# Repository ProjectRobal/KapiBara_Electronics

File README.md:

# KapiBara Electronics Design

That repository holds all the electronics for KapiBara robot. Everything was designed using KiCAD software.

## Boards

- KANGOO - a HAT that connects to Raspberry Pi 5. It delivers +5V using on board buck converter and gives Pi ability to communicate with CAN interface, it also has built in audio codec for microphones ( not used )
- KANGOO_1 - an evolution of KANGOO design it is HAT that connects to Modus extension board, like any other module
- MODUS - an extension board that connect every modules together using standard IDC connectors
- Modus_Extension_Template - a basic template creating standard module compatible with the MODUS board
- MEGANE - a module that handles DC motors control, odometry and orientation estimation using built in IMU and external Magnetrometer
- POWER - a board using for chargin robot's accumulator, it is also responsible for power delivering to entire system
- TWINGO - a module that handles reading state of external touch sensors
- TWINGO_v1.1 - a module that handles reading state of external touch plates, touch is detected by on board RC oscillatros ( not used )

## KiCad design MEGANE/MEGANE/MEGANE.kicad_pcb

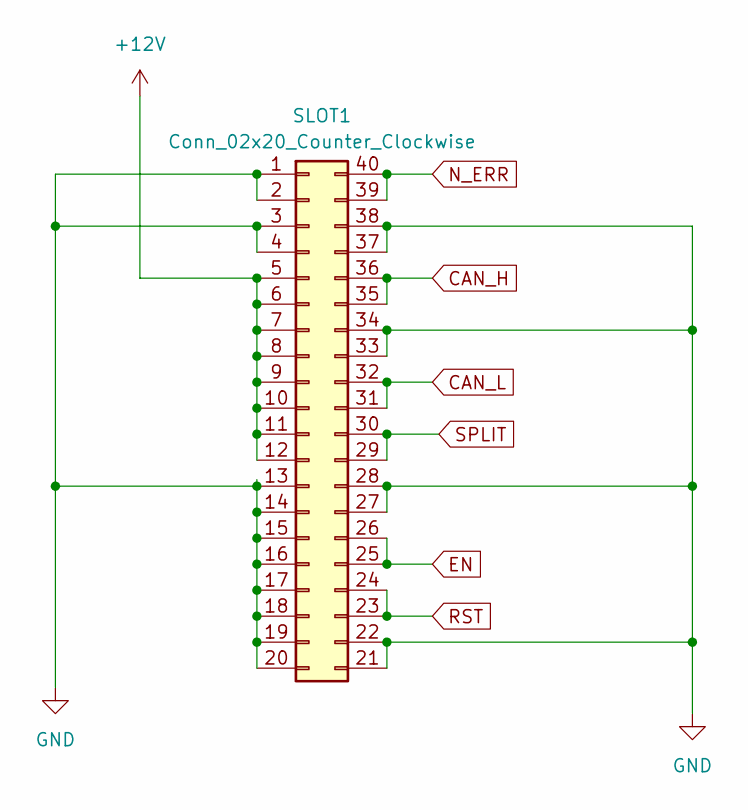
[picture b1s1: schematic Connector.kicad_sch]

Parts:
SLOT1: Conn_02x20_Counter_Clockwise; IDC-Header_2x20_P2.54mm_Horizontal

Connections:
+12V: SLOT1.5, SLOT1.6, SLOT1.7, SLOT1.8, SLOT1.9, SLOT1.10, SLOT1.11, SLOT1.12; also elsewhere on the board
CAN_H: SLOT1.35, SLOT1.36; also elsewhere on the board
CAN_L: SLOT1.31, SLOT1.32; also elsewhere on the board
EN: SLOT1.25, SLOT1.26; also elsewhere on the board
GND: SLOT1.1, SLOT1.2, SLOT1.3, SLOT1.4, SLOT1.13, SLOT1.14, SLOT1.15, SLOT1.16, SLOT1.17, SLOT1.18, SLOT1.19, SLOT1.20, SLOT1.21, SLOT1.22, SLOT1.27, SLOT1.28, SLOT1.33, SLOT1.34, SLOT1.37, SLOT1.38; also elsewhere on the board
N_ERR: SLOT1.39, SLOT1.40; also elsewhere on the board
RST: SLOT1.23, SLOT1.24; also elsewhere on the board
SPLIT: SLOT1.29, SLOT1.30; also elsewhere on the board

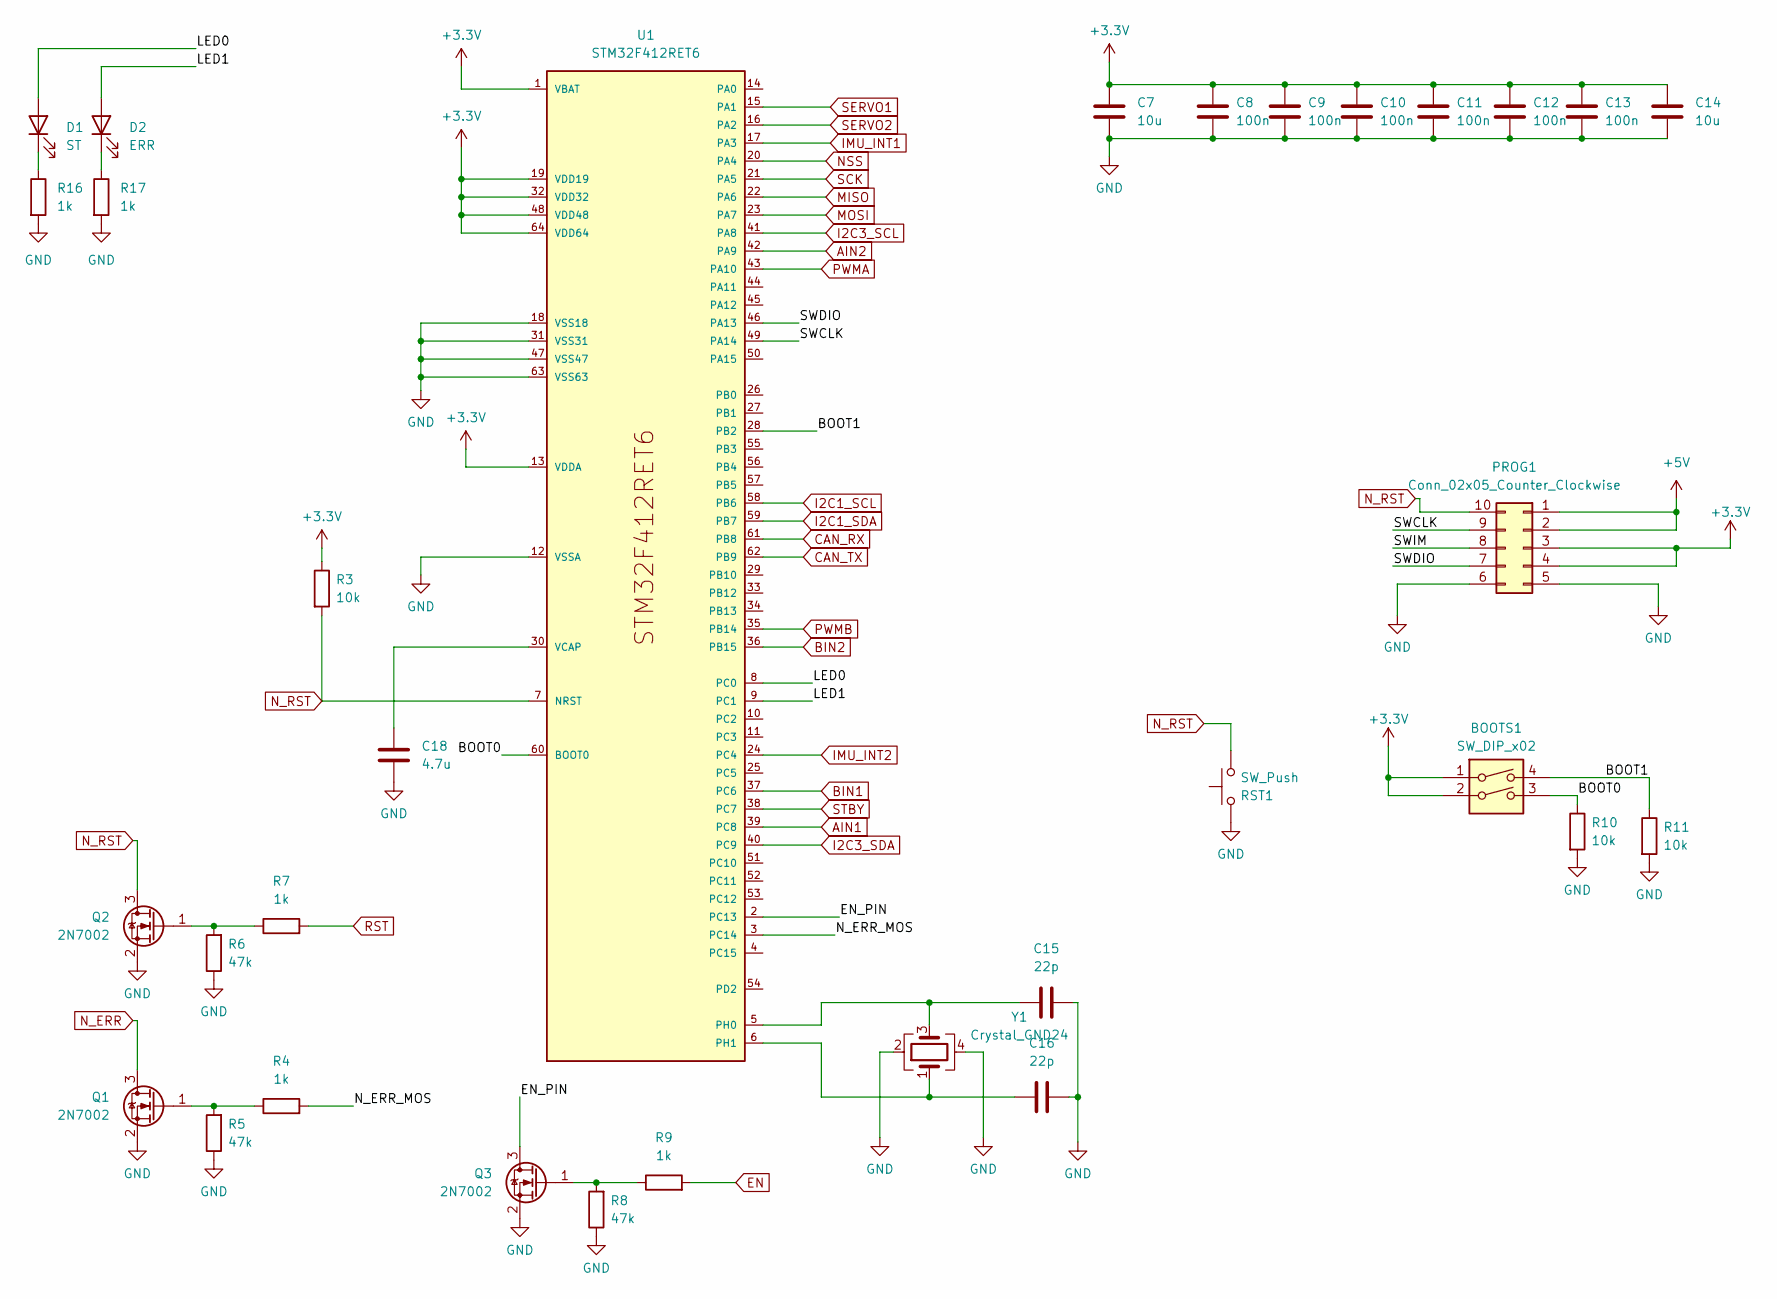
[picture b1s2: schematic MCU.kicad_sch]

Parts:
BOOTS1: SW_DIP_x02; SW_DIP_SPSTx02_Slide_6.7x6.64mm_W8.61mm_P2.54mm_LowProfile
C7, C14: 10u; C_0805_2012Metric_Pad1.18x1.45mm_HandSolder
C8, C9, C10, C11, C12, C13: 100n; C_0603_1608Metric_Pad1.08x0.95mm_HandSolder
C15, C16: 22p; C_0603_1608Metric_Pad1.08x0.95mm_HandSolder
C18: 4.7u; C_0805_2012Metric_Pad1.18x1.45mm_HandSolder
D1: ST; LED_0805_2012Metric_Pad1.15x1.40mm_HandSolder
D2: ERR; LED_0805_2012Metric_Pad1.15x1.40mm_HandSolder
PROG1: Conn_02x05_Counter_Clockwise; IDC-Header_2x05_P2.54mm_Horizontal
Q1, Q2, Q3: 2N7002; SOT-23
R3, R10, R11: 10k; R_0603_1608Metric_Pad0.98x0.95mm_HandSolder
R4, R7, R9, R16, R17: 1k; R_0603_1608Metric_Pad0.98x0.95mm_HandSolder
R5, R6, R8: 47k; R_0603_1608Metric_Pad0.98x0.95mm_HandSolder
RST1: SW_Push; SW_Tactile_SPST_Angled_PTS645Vx39-2LFS
U1: STM32F412RET6; LQFP-10X10-64
Y1: Crystal_GND24; Crystal_SMD_2520-4Pin_2.5x2.0mm

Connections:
+3.3V: BOOTS1.1, BOOTS1.2, C7.1, C8.1, C9.1, C10.1, C11.1, C12.1, C13.1, C14.1, PROG1.3, PROG1.4, R3.1, U1.1 (VBAT), U1.13 (VDDA), U1.19 (VDD19), U1.32 (VDD32), U1.48 (VDD48), U1.64 (VDD64); also elsewhere on the board
+5V: PROG1.1, PROG1.2; also elsewhere on the board
/MCU/BOOT0: BOOTS1.3, R10.1, U1.60 (BOOT0)
/MCU/BOOT1: BOOTS1.4, R11.1, U1.28 (PB2)
/MCU/EN_PIN: Q3.3 (D), U1.2 (PC13)
/MCU/LED0: D1.2 (A), U1.8 (PC0)
/MCU/LED1: D2.2 (A), U1.9 (PC1)
/MCU/N_ERR_MOS: R4.2, U1.3 (PC14)
/MCU/SWCLK: PROG1.9, U1.49 (PA14)
/MCU/SWDIO: PROG1.7, U1.46 (PA13)
/MCU/SWIM: PROG1.8
AIN1: U1.39 (PC8); also elsewhere on the board
AIN2: U1.42 (PA9); also elsewhere on the board
BIN1: U1.37 (PC6); also elsewhere on the board
BIN2: U1.36 (PB15); also elsewhere on the board
CAN_RX: U1.61 (PB8); also elsewhere on the board
CAN_TX: U1.62 (PB9); also elsewhere on the board
EN: R9.2; also elsewhere on the board
GND: C7.2, C8.2, C9.2, C10.2, C11.2, C12.2, C13.2, C14.2, C15.2, C16.2, C18.2, PROG1.5, PROG1.6, Q1.2 (S), Q2.2 (S), Q3.2 (S), R5.1, R6.1, R8.1, R10.2, R11.2, R16.2, R17.2, RST1.2, U1.12 (VSSA), U1.18 (VSS18), U1.31 (VSS31), U1.47 (VSS47), U1.63 (VSS63), Y1.2, Y1.4; also elsewhere on the board
I2C1_SCL: U1.58 (PB6); also elsewhere on the board
I2C1_SDA: U1.59 (PB7); also elsewhere on the board
I2C3_SCL: U1.41 (PA8); also elsewhere on the board
I2C3_SDA: U1.40 (PC9); also elsewhere on the board
IMU_INT1: U1.17 (PA3); also elsewhere on the board
IMU_INT2: U1.24 (PC4)
MISO: U1.22 (PA6)
MOSI: U1.23 (PA7)
NSS: U1.20 (PA4)
N_ERR: Q1.3 (D); also elsewhere on the board
N_RST: PROG1.10, Q2.3 (D), R3.2, RST1.1, U1.7 (NRST)
unnamed: D1.1 (K), R16.1
unnamed: D2.1 (K), R17.1
unnamed: Q1.1 (G), R4.1, R5.2
unnamed: Q2.1 (G), R6.2, R7.1
unnamed: Q3.1 (G), R8.2, R9.1
unnamed: C15.1, U1.5 (PH0), Y1.3
unnamed: C16.1, U1.6 (PH1), Y1.1
unnamed: C18.1, U1.30 (VCAP)
PWMA: U1.43 (PA10); also elsewhere on the board
PWMB: U1.35 (PB14); also elsewhere on the board
RST: R7.2; also elsewhere on the board
SCK: U1.21 (PA5)
SERVO1: U1.15 (PA1); also elsewhere on the board
SERVO2: U1.16 (PA2); also elsewhere on the board
STBY: U1.38 (PC7); also elsewhere on the board

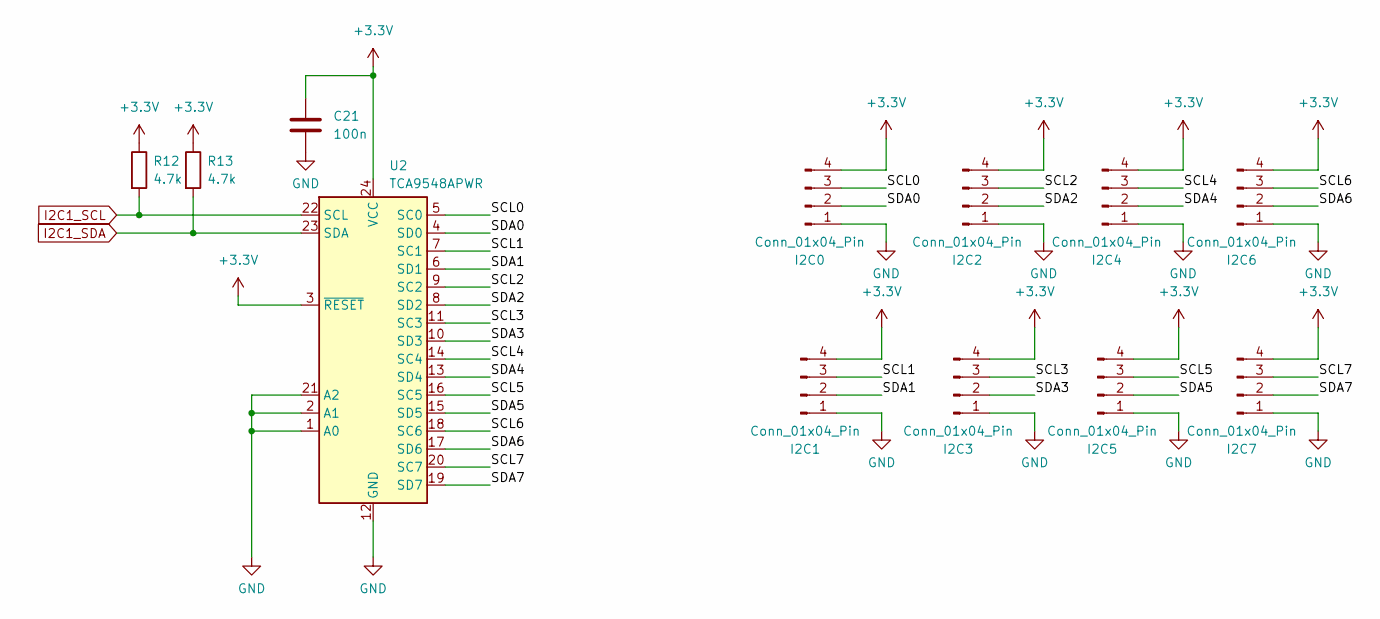
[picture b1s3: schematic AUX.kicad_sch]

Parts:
C21: 100n; C_0603_1608Metric_Pad1.08x0.95mm_HandSolder
I2C0, I2C1, I2C2, I2C3, I2C4, I2C5, I2C6, I2C7: Conn_01x04_Pin; JST_XH_B4B-XH-A_1x04_P2.50mm_Vertical
R12, R13: 4.7k; R_0603_1608Metric_Pad0.98x0.95mm_HandSolder
U2: TCA9548APWR; TSSOP-24_4.4x7.8mm_P0.65mm

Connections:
+3.3V: C21.2, I2C0.4, I2C1.4, I2C2.4, I2C3.4, I2C4.4, I2C5.4, I2C6.4, I2C7.4, R12.1, R13.1, U2.3 (~RESET), U2.24 (VCC); also elsewhere on the board
/AUX/SCL0: I2C0.3, U2.5 (SC0)
/AUX/SCL1: I2C1.3, U2.7 (SC1)
/AUX/SCL2: I2C2.3, U2.9 (SC2)
/AUX/SCL3: I2C3.3, U2.11 (SC3)
/AUX/SCL4: I2C4.3, U2.14 (SC4)
/AUX/SCL5: I2C5.3, U2.16 (SC5)
/AUX/SCL6: I2C6.3, U2.18 (SC6)
/AUX/SCL7: I2C7.3, U2.20 (SC7)
/AUX/SDA0: I2C0.2, U2.4 (SD0)
/AUX/SDA1: I2C1.2, U2.6 (SD1)
/AUX/SDA2: I2C2.2, U2.8 (SD2)
/AUX/SDA3: I2C3.2, U2.10 (SD3)
/AUX/SDA4: I2C4.2, U2.13 (SD4)
/AUX/SDA5: I2C5.2, U2.15 (SD5)
/AUX/SDA6: I2C6.2, U2.17 (SD6)
/AUX/SDA7: I2C7.2, U2.19 (SD7)
GND: C21.1, I2C0.1, I2C1.1, I2C2.1, I2C3.1, I2C4.1, I2C5.1, I2C6.1, I2C7.1, U2.1 (A0), U2.2 (A1), U2.12 (GND), U2.21 (A2); also elsewhere on the board
I2C1_SCL: R12.2, U2.22 (SCL); also elsewhere on the board
I2C1_SDA: R13.2, U2.23 (SDA); also elsewhere on the board

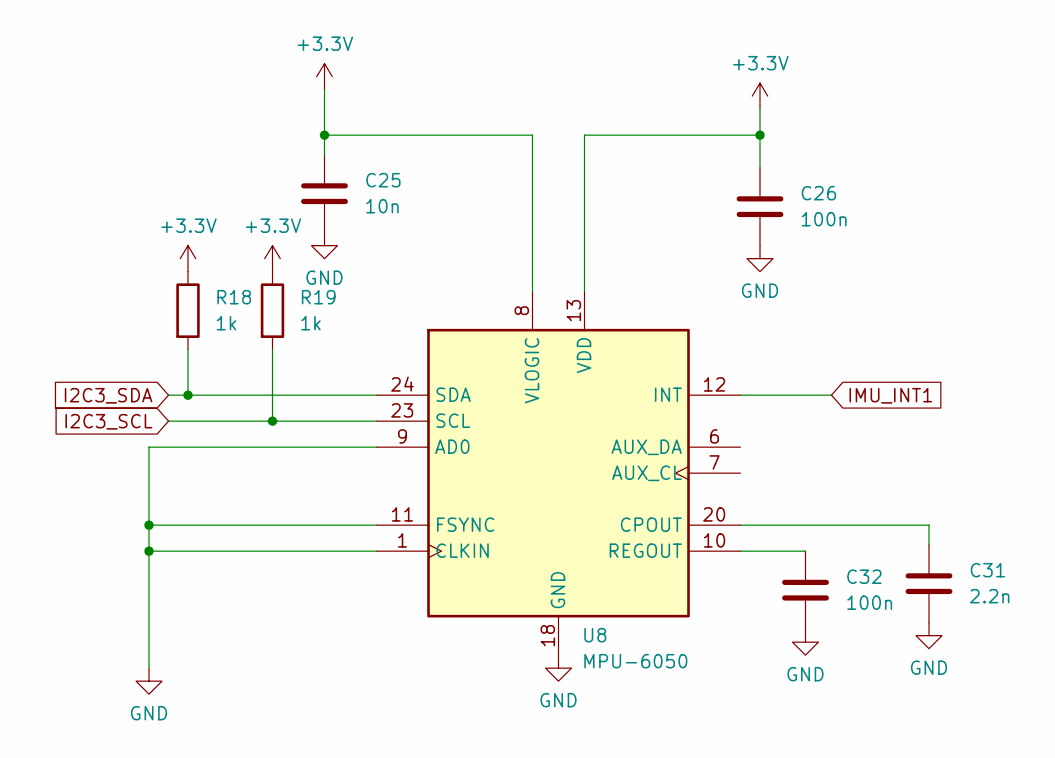
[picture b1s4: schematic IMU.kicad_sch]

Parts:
C25: 10n; C_0603_1608Metric_Pad1.08x0.95mm_HandSolder
C26, C32: 100n; C_0603_1608Metric_Pad1.08x0.95mm_HandSolder
C31: 2.2n; C_0603_1608Metric_Pad1.08x0.95mm_HandSolder
R18, R19: 1k; R_0603_1608Metric_Pad0.98x0.95mm_HandSolder
U8: MPU-6050; InvenSense_QFN-24_4x4mm_P0.5mm_NoMask

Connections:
+3.3V: C25.2, C26.2, R18.1, R19.1, U8.8 (VLOGIC), U8.13 (VDD); also elsewhere on the board
GND: C25.1, C26.1, C31.1, C32.1, U8.1 (CLKIN), U8.9 (AD0), U8.11 (FSYNC), U8.18 (GND); also elsewhere on the board
I2C3_SCL: R19.2, U8.23 (SCL); also elsewhere on the board
I2C3_SDA: R18.2, U8.24 (SDA); also elsewhere on the board
IMU_INT1: U8.12 (INT); also elsewhere on the board
unnamed: C31.2, U8.20 (CPOUT)
unnamed: C32.2, U8.10 (REGOUT)

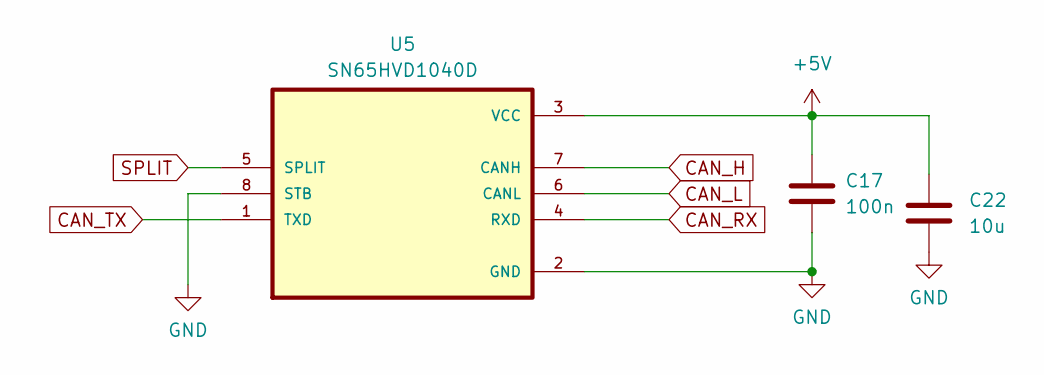
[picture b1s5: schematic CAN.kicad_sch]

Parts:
C17: 100n; C_0603_1608Metric_Pad1.08x0.95mm_HandSolder
C22: 10u; C_0805_2012Metric_Pad1.18x1.45mm_HandSolder
U5: SN65HVD1040D; SOIC127P599X175-8N

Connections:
+5V: C17.1, C22.1, U5.3 (VCC); also elsewhere on the board
CAN_H: U5.7 (CANH); also elsewhere on the board
CAN_L: U5.6 (CANL); also elsewhere on the board
CAN_RX: U5.4 (RXD); also elsewhere on the board
CAN_TX: U5.1 (TXD); also elsewhere on the board
GND: C17.2, C22.2, U5.2 (GND), U5.8 (STB); also elsewhere on the board
SPLIT: U5.5 (SPLIT); also elsewhere on the board

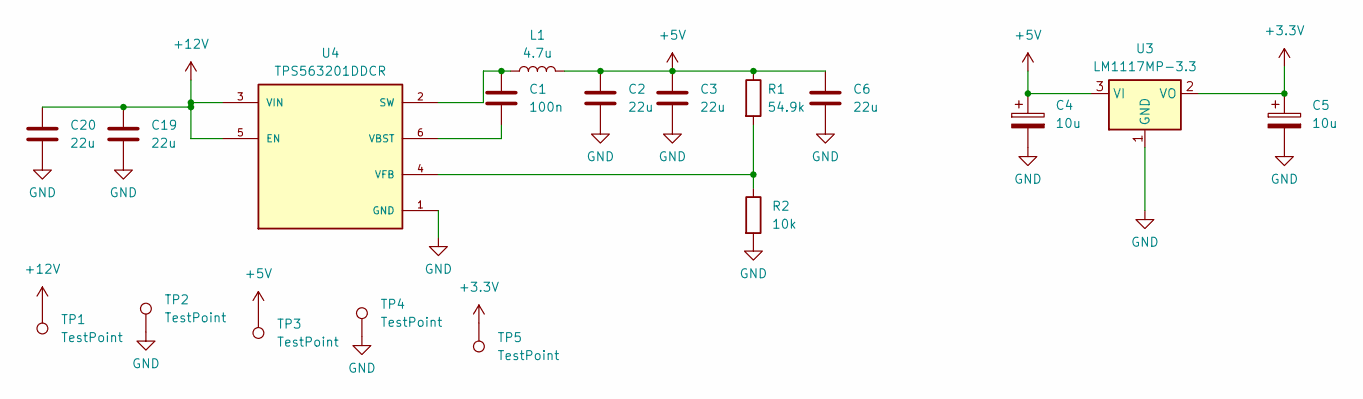
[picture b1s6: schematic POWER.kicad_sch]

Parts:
C1: 100n; C_0603_1608Metric_Pad1.08x0.95mm_HandSolder
C2, C3, C6, C19, C20: 22u; C_0805_2012Metric_Pad1.18x1.45mm_HandSolder
C4, C5: 10u; CP_EIA-3528-21_Kemet-B_Pad1.50x2.35mm_HandSolder
L1: 4.7u; L_Changjiang_FNR6045S
R1: 54.9k; R_0603_1608Metric_Pad0.98x0.95mm_HandSolder
R2: 10k; R_0603_1608Metric_Pad0.98x0.95mm_HandSolder
TP1, TP3, TP5: TestPoint; TestPoint_Pad_D3.0mm
TP2, TP4: TestPoint; TestPoint_Pad_3.0x3.0mm
U3: LM1117MP-3.3; SOT-223
U4: TPS563201DDCR; SOT95P280X110-6N; PARTREV December 2015

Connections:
+3.3V: C5.1, TP5.1, U3.2 (VO); also elsewhere on the board
+5V: C2.1, C3.1, C4.1, C6.1, L1.2, R1.1, TP3.1, U3.3 (VI); also elsewhere on the board
+12V: C19.1, C20.1, TP1.1, U4.3 (VIN), U4.5 (EN); also elsewhere on the board
GND: C2.2, C3.2, C4.2, C5.2, C6.2, C19.2, C20.2, R2.2, TP2.1, TP4.1, U3.1 (GND), U4.1 (GND); also elsewhere on the board
unnamed: C1.2, L1.1, U4.2 (SW)
unnamed: C1.1, U4.6 (VBST)
unnamed: R1.2, R2.1, U4.4 (VFB)

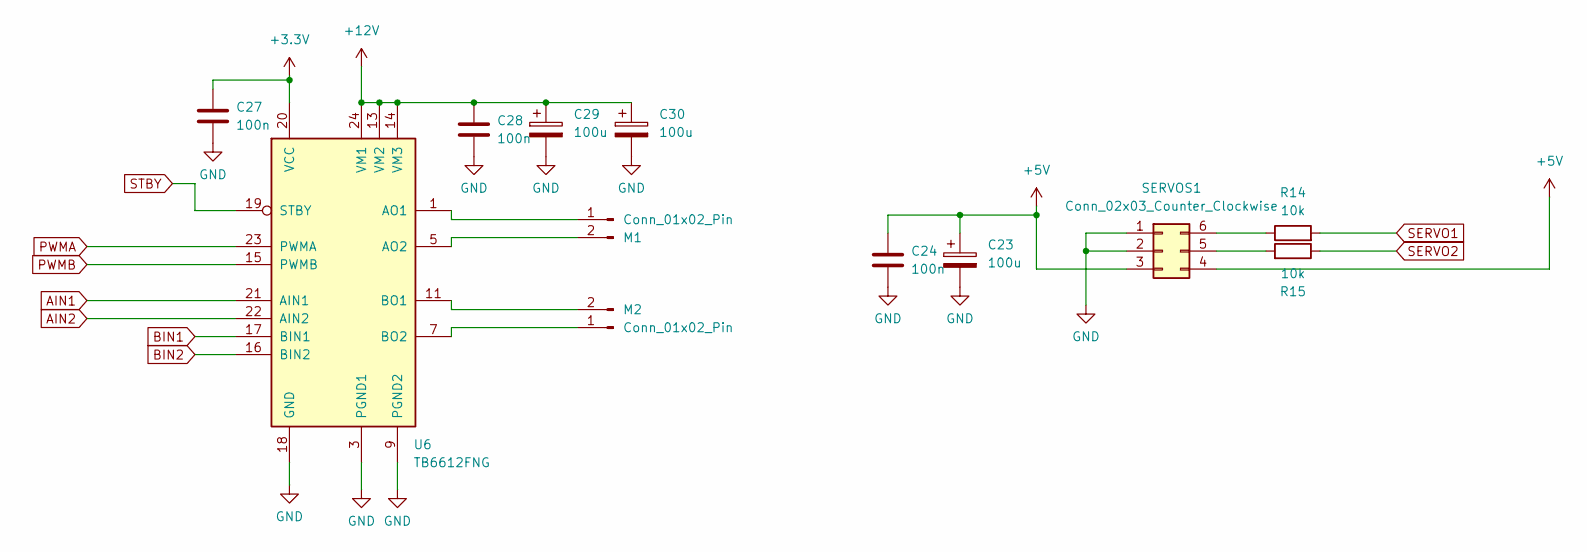
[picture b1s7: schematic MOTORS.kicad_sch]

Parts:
C23, C29, C30: 100u; CP_EIA-7132-28_AVX-C_Pad2.72x3.50mm_HandSolder
C24, C27, C28: 100n; C_0603_1608Metric_Pad1.08x0.95mm_HandSolder
M1, M2: Conn_01x02_Pin; AMASS_XT30PW-M_1x02_P2.50mm_Horizontal
R14, R15: 10k; R_0603_1608Metric_Pad0.98x0.95mm_HandSolder
SERVOS1: Conn_02x03_Counter_Clockwise; PinHeader_2x03_P2.54mm_Horizontal
U6: TB6612FNG; SSOP-24_5.3x8.2mm_P0.65mm

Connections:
+3.3V: C27.1, U6.20 (VCC); also elsewhere on the board
+5V: C23.1, C24.1, SERVOS1.3, SERVOS1.4; also elsewhere on the board
+12V: C28.1, C29.1, C30.1, U6.13 (VM2), U6.14 (VM3), U6.24 (VM1); also elsewhere on the board
AIN1: U6.21 (AIN1); also elsewhere on the board
AIN2: U6.22 (AIN2); also elsewhere on the board
BIN1: U6.17 (BIN1); also elsewhere on the board
BIN2: U6.16 (BIN2); also elsewhere on the board
GND: C23.2, C24.2, C27.2, C28.2, C29.2, C30.2, SERVOS1.1, SERVOS1.2, U6.3 (PGND1), U6.4 (PGND1), U6.9 (PGND2), U6.10 (PGND2), U6.18 (GND); also elsewhere on the board
unnamed: M1.1, U6.1 (AO1), U6.2 (AO1)
unnamed: M1.2, U6.5 (AO2), U6.6 (AO2)
unnamed: M2.1, U6.7 (BO2), U6.8 (BO2)
unnamed: M2.2, U6.11 (BO1), U6.12 (BO1)
unnamed: R15.2, SERVOS1.5
unnamed: R14.1, SERVOS1.6
PWMA: U6.23 (PWMA); also elsewhere on the board
PWMB: U6.15 (PWMB); also elsewhere on the board
SERVO1: R14.2; also elsewhere on the board
SERVO2: R15.1; also elsewhere on the board
STBY: U6.19 (STBY); also elsewhere on the board

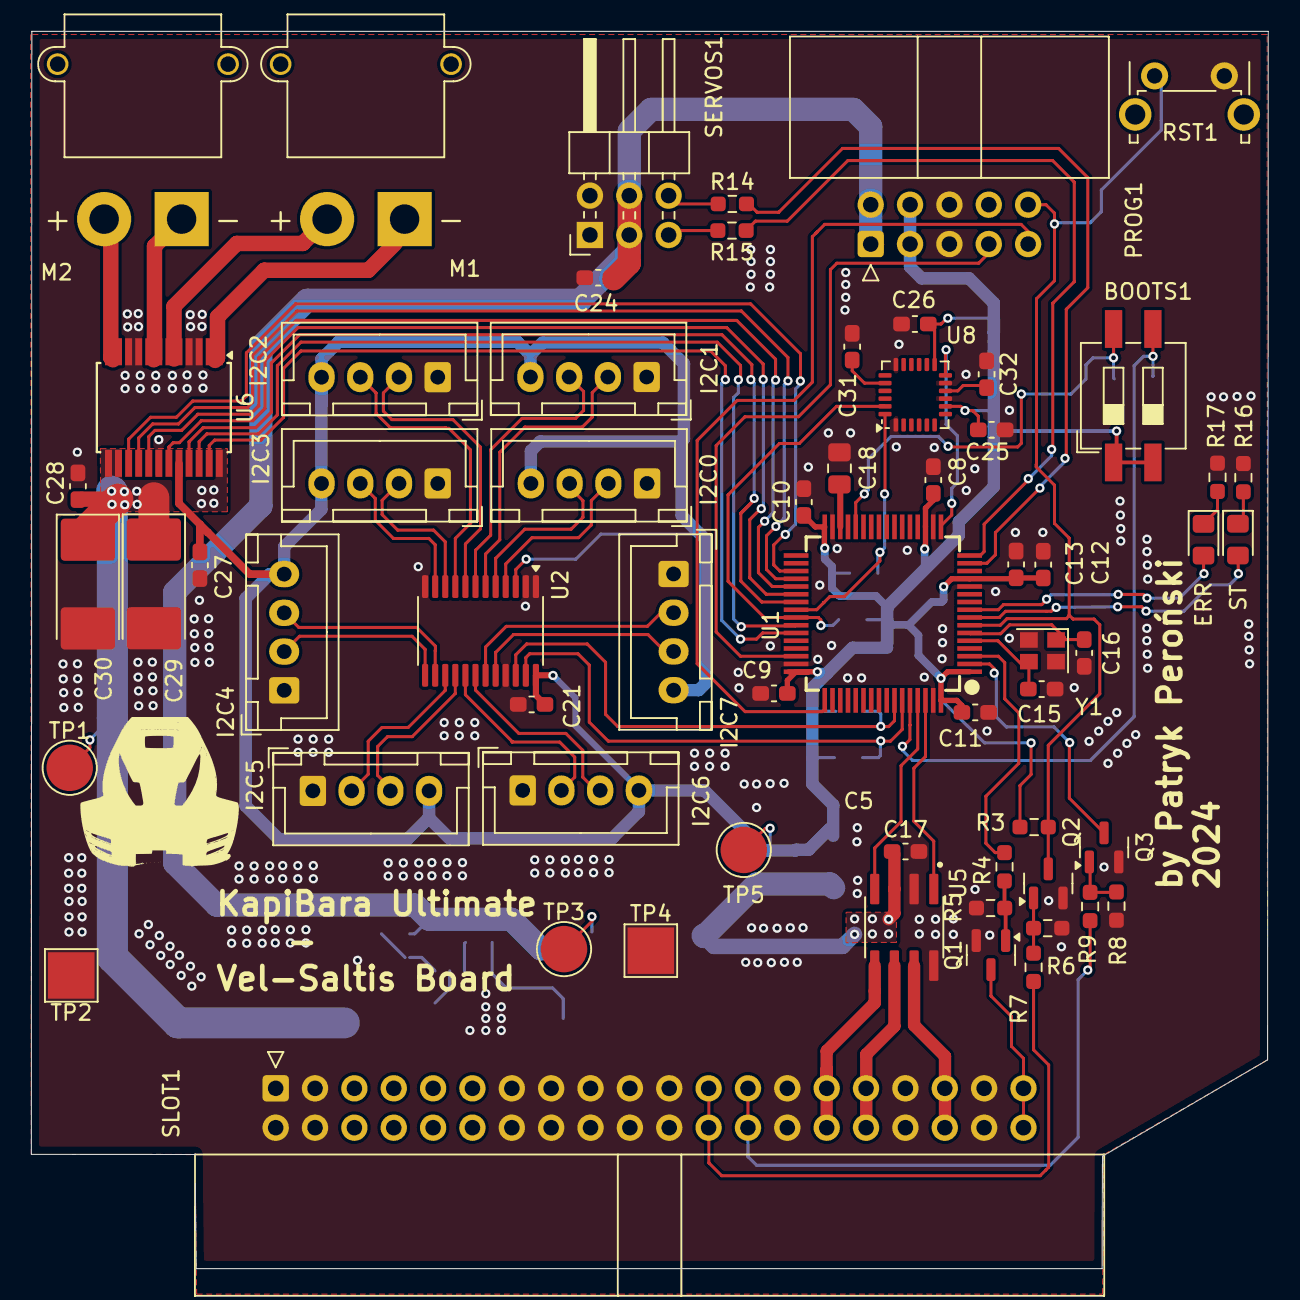
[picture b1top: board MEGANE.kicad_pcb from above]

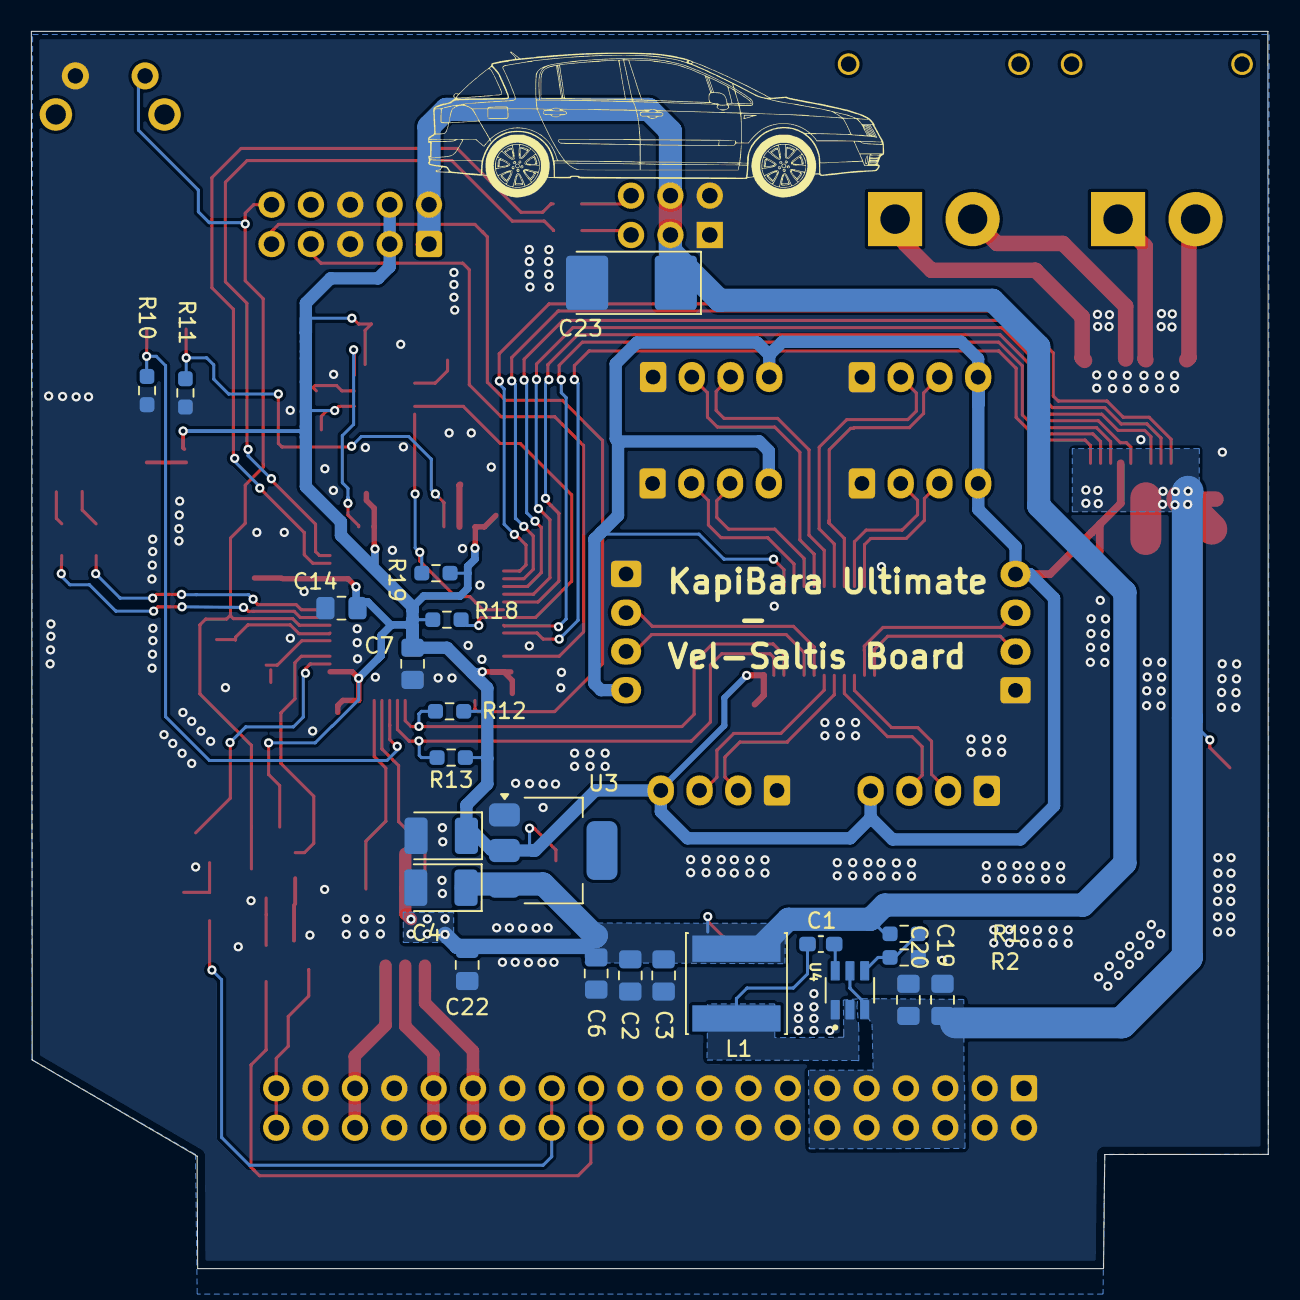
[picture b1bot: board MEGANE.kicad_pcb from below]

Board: 2 copper layers, 79.8 x 79.8 mm, 85 parts (23 on the bottom side), 70 nets.

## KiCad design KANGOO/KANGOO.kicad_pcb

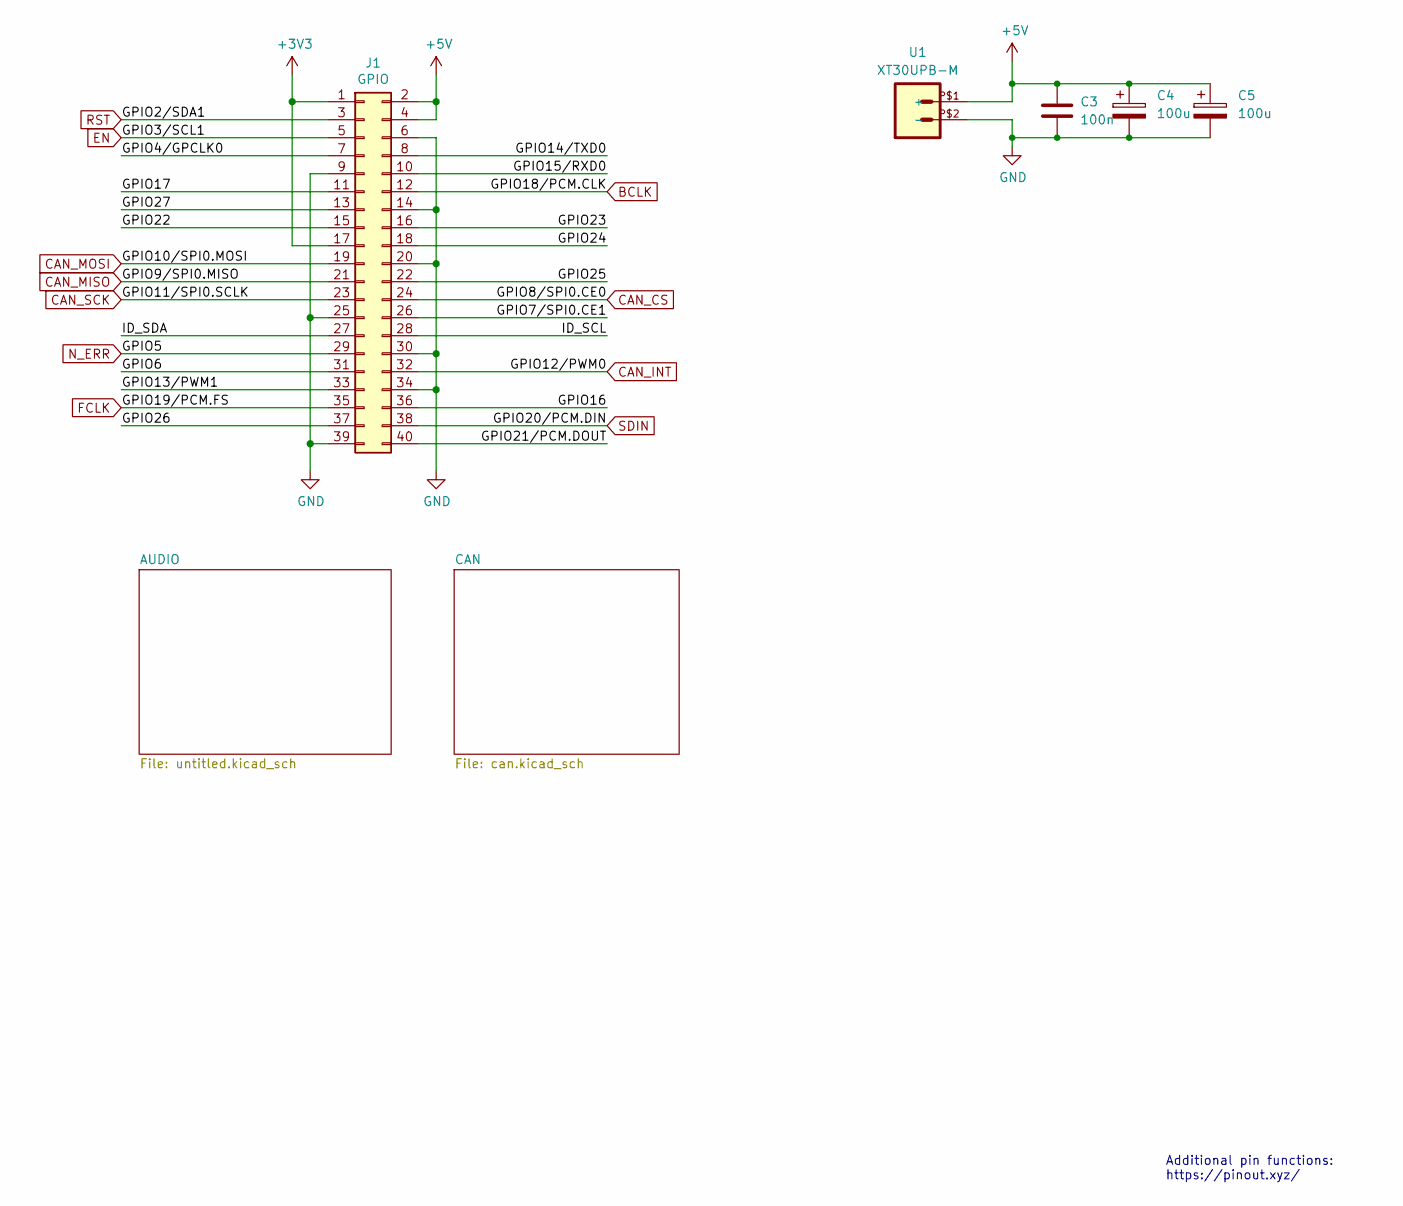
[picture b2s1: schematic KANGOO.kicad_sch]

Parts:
C3: 100n; C_0603_1608Metric_Pad1.08x0.95mm_HandSolder
C4, C5: 100u; CP_EIA-7132-28_AVX-C_Pad2.72x3.50mm_HandSolder
J1: GPIO; PinSocket_2x20_P2.54mm_Vertical
U1: XT30UPB-M

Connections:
+3V3: J1.1, J1.17
+5V: C3.1, C4.1, C5.1, J1.2, J1.4, U1.P$1 (+); also elsewhere on the board
/GPIO4/GPCLK0: J1.7
/GPIO6: J1.31
/GPIO7/SPI0.CE1: J1.26
/GPIO13/PWM1: J1.33
/GPIO14/TXD0: J1.8
/GPIO15/RXD0: J1.10
/GPIO16: J1.36
/GPIO17: J1.11
/GPIO21/PCM.DOUT: J1.40
/GPIO22: J1.15
/GPIO23: J1.16
/GPIO24: J1.18
/GPIO25: J1.22
/GPIO26: J1.37
/GPIO27: J1.13
/ID_SCL: J1.28
/ID_SDA: J1.27
BCLK: J1.12; also elsewhere on the board
CAN_CS: J1.24; also elsewhere on the board
CAN_INT: J1.32; also elsewhere on the board
CAN_MISO: J1.21; also elsewhere on the board
CAN_MOSI: J1.19; also elsewhere on the board
CAN_SCK: J1.23; also elsewhere on the board
EN: J1.5; also elsewhere on the board
FCLK: J1.35; also elsewhere on the board
GND: C3.2, C4.2, C5.2, J1.6, J1.9, J1.14, J1.20, J1.25, J1.30, J1.34, J1.39, U1.P$2 (-); also elsewhere on the board
N_ERR: J1.29; also elsewhere on the board
RST: J1.3; also elsewhere on the board
SDIN: J1.38; also elsewhere on the board

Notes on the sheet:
Additional pin functions: https://pinout.xyz/

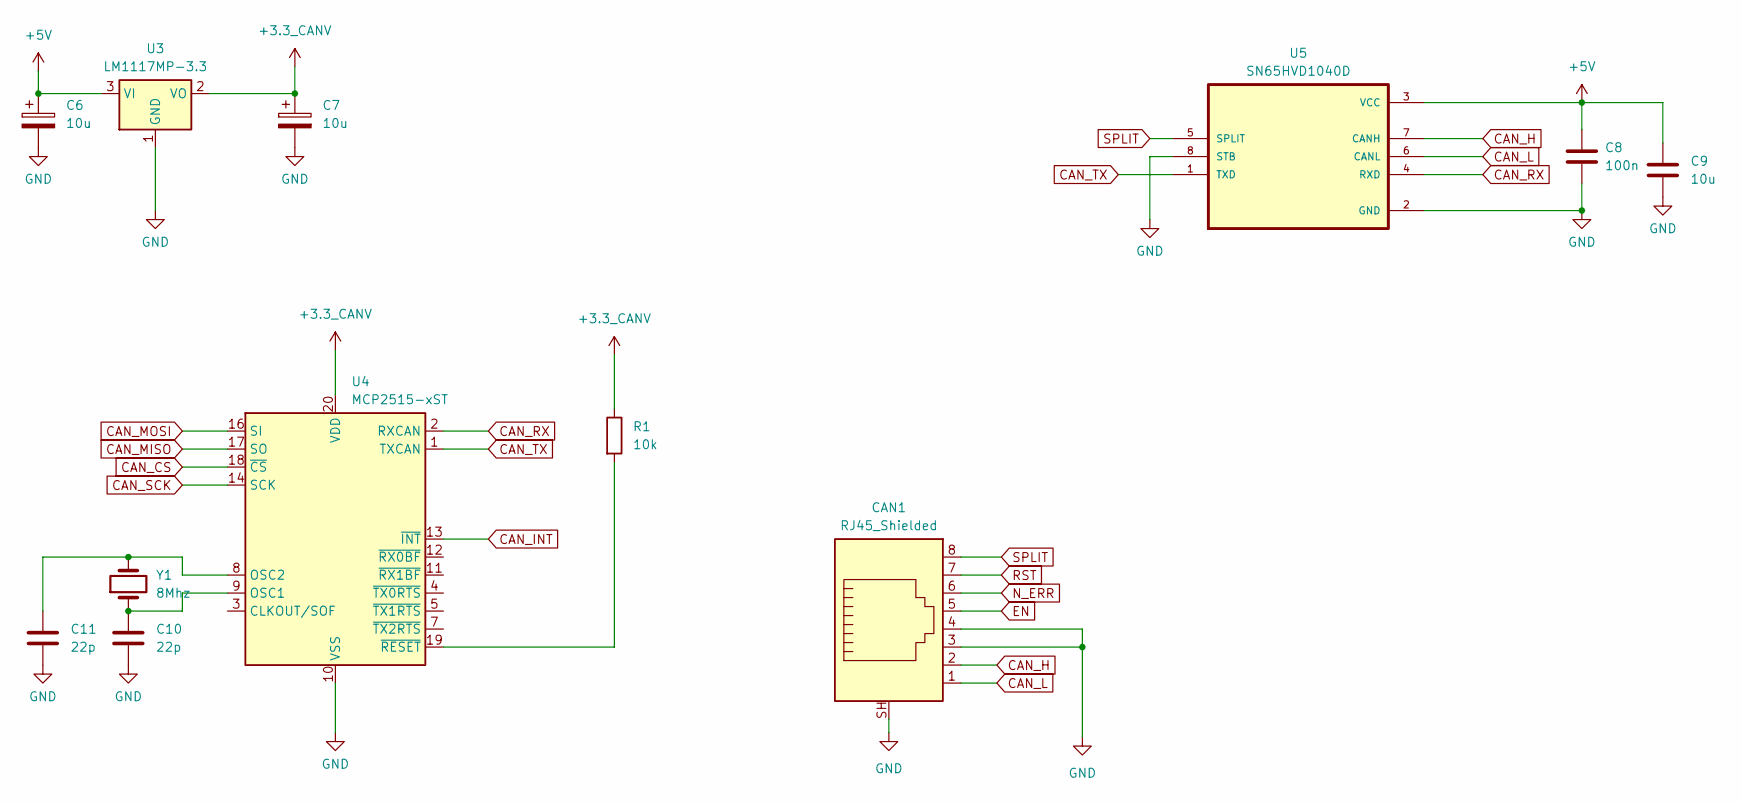
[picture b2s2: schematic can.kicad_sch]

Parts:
C6, C7: 10u; CP_EIA-3528-21_Kemet-B_Pad1.50x2.35mm_HandSolder
C8: 100n; C_0603_1608Metric_Pad1.08x0.95mm_HandSolder
C9: 10u; C_0805_2012Metric_Pad1.18x1.45mm_HandSolder
C10, C11: 22p; C_0603_1608Metric_Pad1.08x0.95mm_HandSolder
CAN1: RJ45_Shielded; RJ45_HALO_HFJ11-x2450HRL_Horizontal
R1: 10k; R_0603_1608Metric_Pad0.98x0.95mm_HandSolder
U3: LM1117MP-3.3; SOT-223
U4: MCP2515-xST; TSSOP-20_4.4x6.5mm_P0.65mm
U5: SN65HVD1040D; SOIC127P599X175-8N
Y1: 8Mhz; Crystal_HC49-U_Vertical

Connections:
+3.3_CANV: C7.1, R1.1, U3.2 (VO), U4.20 (VDD)
+5V: C6.1, C8.1, C9.1, U3.3 (VI), U5.3 (VCC); also elsewhere on the board
CAN_CS: U4.18 (~CS); also elsewhere on the board
CAN_H: CAN1.2, U5.7 (CANH)
CAN_INT: U4.13 (~INT); also elsewhere on the board
CAN_L: CAN1.1, U5.6 (CANL)
CAN_MISO: U4.17 (SO); also elsewhere on the board
CAN_MOSI: U4.16 (SI); also elsewhere on the board
CAN_RX: U4.2 (RXCAN), U5.4 (RXD)
CAN_SCK: U4.14 (SCK); also elsewhere on the board
CAN_TX: U4.1 (TXCAN), U5.1 (TXD)
EN: CAN1.5; also elsewhere on the board
GND: C6.2, C7.2, C8.2, C9.2, C10.2, C11.2, CAN1.3, CAN1.4, CAN1.SH, U3.1 (GND), U4.10 (VSS), U5.2 (GND), U5.8 (STB); also elsewhere on the board
N_ERR: CAN1.6; also elsewhere on the board
unnamed: C10.1, U4.9 (OSC1), Y1.1
unnamed: C11.1, U4.8 (OSC2), Y1.2
unnamed: R1.2, U4.19 (~RESET)
RST: CAN1.7; also elsewhere on the board
SPLIT: CAN1.8, U5.5 (SPLIT)

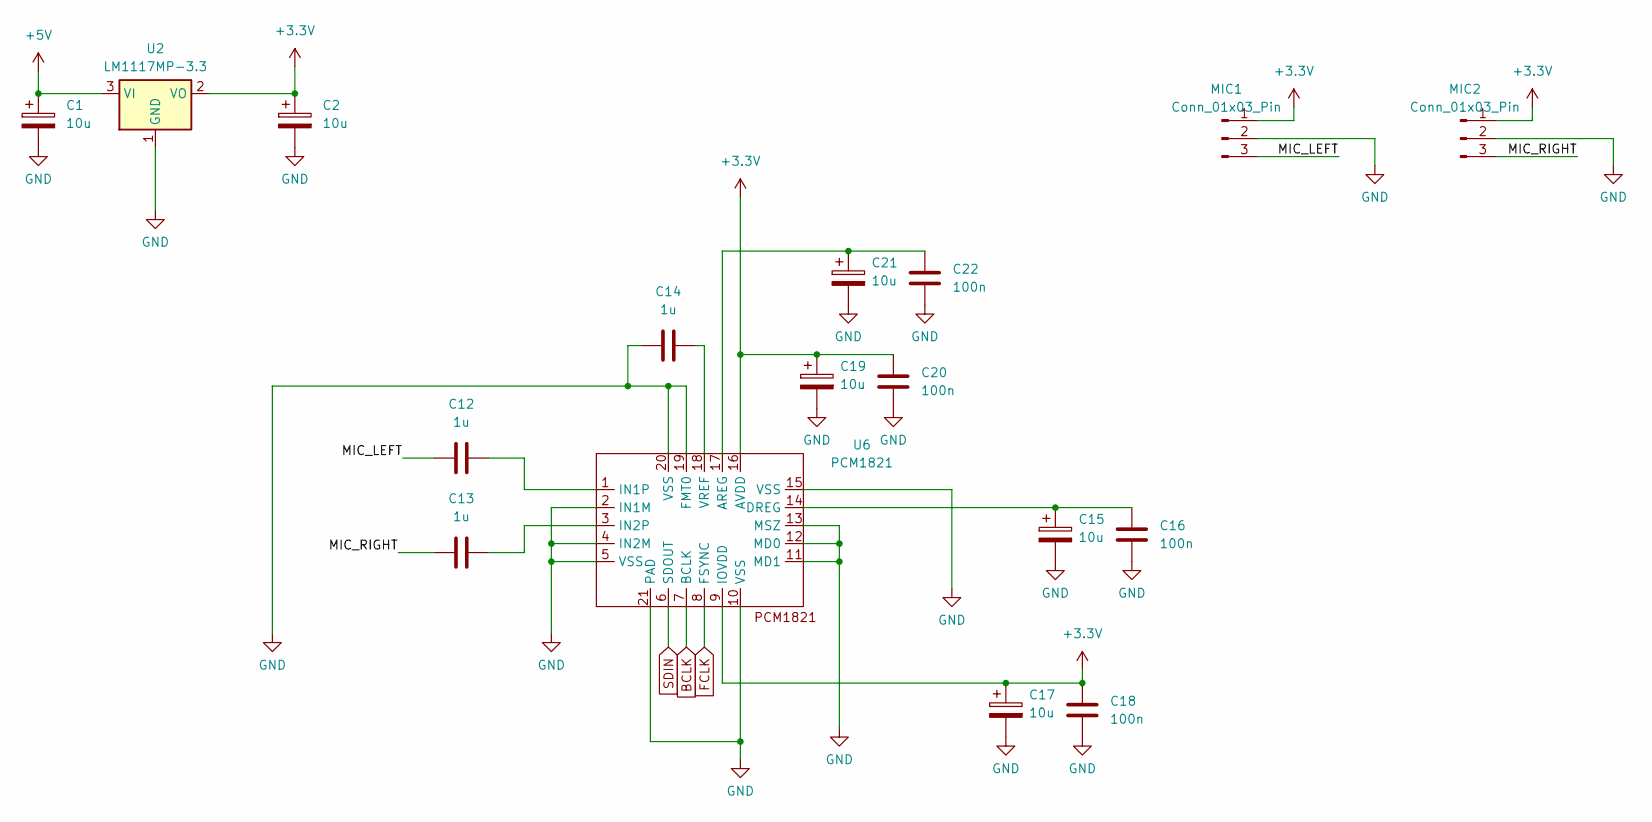
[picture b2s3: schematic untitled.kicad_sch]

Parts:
C1, C2, C15, C17, C19, C21: 10u; CP_EIA-3528-21_Kemet-B_Pad1.50x2.35mm_HandSolder
C12, C13, C14: 1u; C_0805_2012Metric_Pad1.18x1.45mm_HandSolder
C16, C18, C20, C22: 100n; C_0603_1608Metric_Pad1.08x0.95mm_HandSolder
MIC1, MIC2: Conn_01x03_Pin; JST_XH_B3B-XH-AM_1x03_P2.50mm_Vertical
U2: LM1117MP-3.3; SOT-223
U6: PCM1821; WQFN-16

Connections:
+3.3V: C2.1, C17.1, C18.1, C19.1, C20.1, MIC1.1, MIC2.1, U2.2 (VO), U6.9 (IOVDD), U6.16 (AVDD)
+5V: C1.1, U2.3 (VI); also elsewhere on the board
/AUDIO/MIC_LEFT: C12.1, MIC1.3
/AUDIO/MIC_RIGHT: C13.1, MIC2.3
BCLK: U6.7 (BCLK); also elsewhere on the board
FCLK: U6.8 (FSYNC); also elsewhere on the board
GND: C1.2, C2.2, C14.1, C15.2, C16.2, C17.2, C18.2, C19.2, C20.2, C21.2, C22.2, MIC1.2, MIC2.2, U2.1 (GND), U6.2 (IN1M), U6.4 (IN2M), U6.5 (VSS), U6.10 (VSS), U6.11 (MD1), U6.12 (MD0), U6.13 (MSZ), U6.15 (VSS), U6.19 (FMT0), U6.20 (VSS), U6.21 (PAD); also elsewhere on the board
unnamed: C21.1, C22.1, U6.17 (AREG)
unnamed: C15.1, C16.1, U6.14 (DREG)
unnamed: C12.2, U6.1 (IN1P)
unnamed: C13.2, U6.3 (IN2P)
unnamed: C14.2, U6.18 (VREF)
SDIN: U6.6 (SDOUT); also elsewhere on the board
